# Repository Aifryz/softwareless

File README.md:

# Softwareless

What if, all software disappeared?

## Background

A few years ago, I saw a reddit post in which the OP asked if it would be possible to program a regular PC without using another PC. You would not be able to download any existing software from a network, install software from flash drives, CDs, etc.

The question also asked what would be the minimal amount of software needed to accomplish this goal.

The consensus was, that to do that you would need at least a piece of software that could write to arbitrary memory locations. From there you could write an editor, a compiler, and other software.

That answer never really satisfied me, from point of view of an embedded developer, one knows that the software running on the PC is only a small part of the puzzle. There's probably software running on the keyboard, disk drives, and of course, there's BIOS. So a modern PC probably could not be programmed without the help of any external software.

But what about designing a computer, in such a way that this would be possible?

This of course has been done in the past, first programs running on first computers could not be compiled since there were no compilers/assemblers available, ... since those would count as the first programs. Back then, people used various ways of getting programs onto computers: manually weaving wires in core rope memory, using switches in front of computers to arbitrarily modify memory, etc. So it's known that's possible, but just how hard would it be to replicate, given the last 70-ish years of progress?

## Why

With this project I want to accomplish some personal goals:

* create a RISC-V core

* create an OS

* design language and create a compiler for it

* design and develop some hardware able to support the previous goals

## Rules

* No external software can be run on the Computer
* Every automation has to be done on the Computer only
  * e.g. you cannot just compile software on a regular PC and then just type compiled program into the Computer
  * text editors are ok, just no macros, scripting, etc.
  * EDA tools can only be used to create hardware, you cannot use them to load ROMs into memory.
* No external HDL and hardware design: all HDL has to be created from scratch, same for schematics and board designs
  * I'll allow copying reference designs, provided by device manufacturers
* Omniscience: you may use every resource available to further your knowledge

Yes, I know the rules are very NIHish, I hope that by following those rules I finally get sick of reinventing the wheel and decide to use more ready libraries in the future :)

## Goals

*   Create a RISC-V processor
  * Device agnostic HDL, it has to be able to be synthesized on most of available FPGAs
*   Design and assemble terminal capable of interfacing with the designed RISC-V processor
  * keyboard
  * text display
  * CPU interface/protocol
* Design and create a basic set of software
  * text editor
  * file system
  * shell
* assembler
* Design a language and create a compiler for it
* Add a video capability to the processor system
  * text and graphics
  * some color
* Add networking
  * build a second board with working CPU
  * connect them
  * exchange data

And for the ultimate goal: I want to be able to do the thing that the computers were solely designed for, taking pictures of cats and sending them to each other :)

This list does not contain all goals that will be achieved and will be modified in time.

## Licensing

If not specified otherwise, all software in this repository is licensed under MIT license, all hardware is licensed under CERN-OHL-P
Logo is licensed under CC BY-SA 3.0

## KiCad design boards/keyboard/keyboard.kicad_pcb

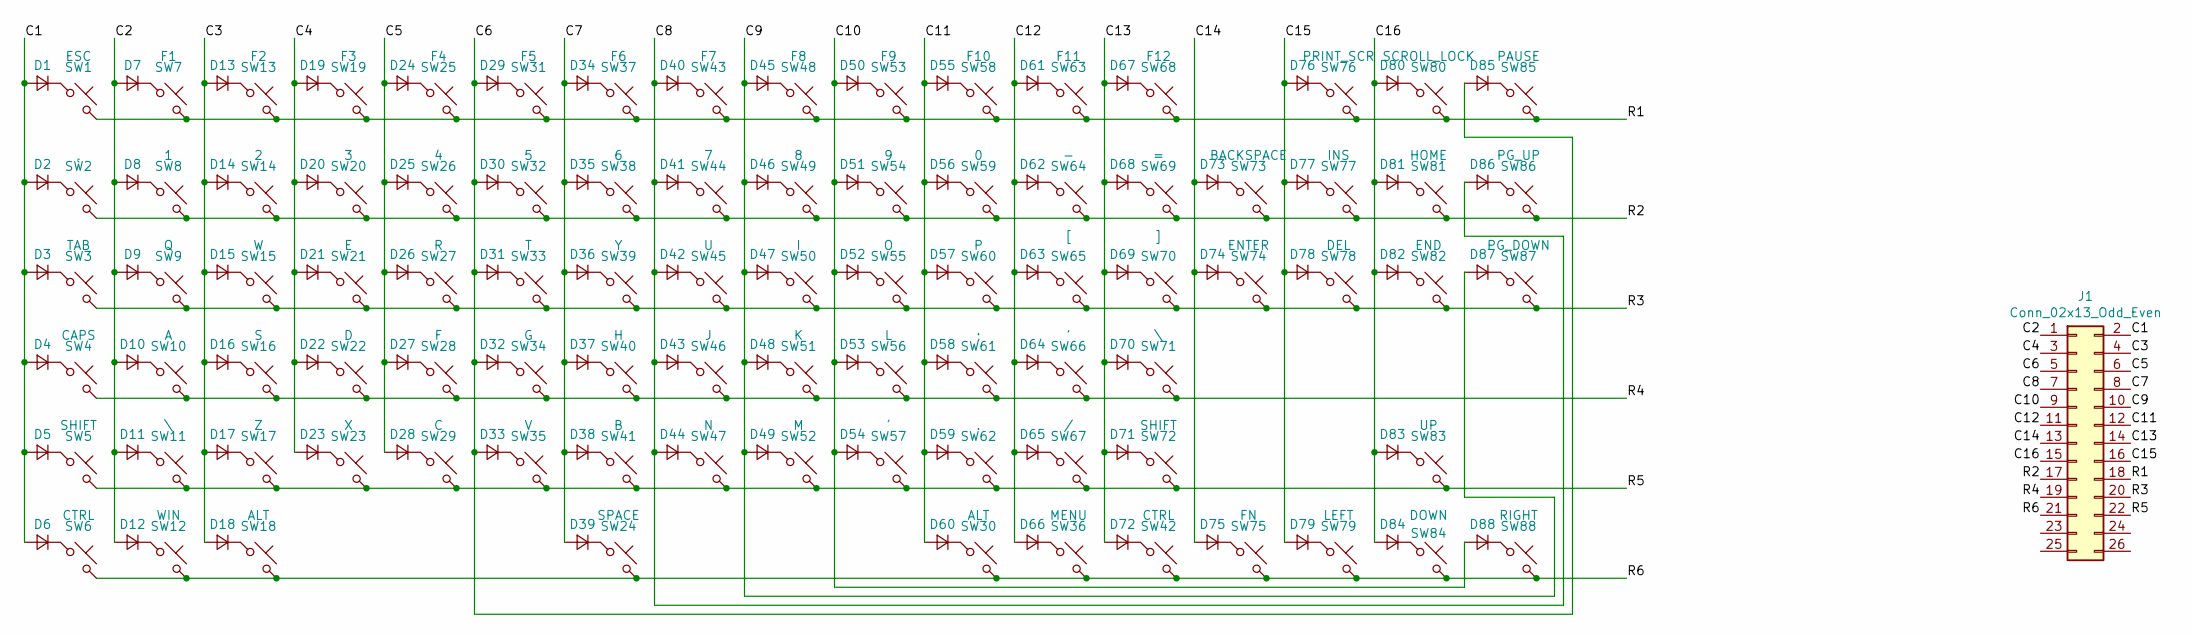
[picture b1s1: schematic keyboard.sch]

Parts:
D1, D2, D3, D4, D5, D7, D8, D9, D10, D11, D12, D13, D14, D15, D16, D17, D18, D19, D20, D21, D22, D23, D24, D25, D26, D27, D28, D29, D30, D31, D32, D33, D34, D35, D36, D37, D38, D39, D40, D41, D42, D43, D44, D45, D46, D47, D48, D49, D50, D51, D52, D53, D54, D55, D56, D57, D58, D59, D60, D61, D62, D63, D64, D65, D66, D67, D68, D69, D70, D71, D72, D73, D74, D75, D76, D77, D78, D79, D80, D81, D82, D83, D84, D85, D86, D87, D88: D_Small; D_SOD-323_HandSoldering
D6: Diode_SMD:D_SOD-323_HandSoldering; D_SOD-323_HandSoldering
J1: Conn_02x13_Odd_Even; IDC-Header_2x13_P2.54mm_Horizontal
SW1: ESC; SW_Cherry_MX_1.00u_PCB
SW2: ~`; SW_Cherry_MX_1.00u_PCB
SW3: TAB; SW_Cherry_MX_1.50u_PCB
SW4: CAPS; SW_Cherry_MX_1.75u_PCB
SW5: SHIFT; SW_Cherry_MX_1.25u_PCB
SW6: CTRL; SW_Cherry_MX_1.50u_PCB
SW7: F1; SW_Cherry_MX_1.00u_PCB
SW8: 1; SW_Cherry_MX_1.00u_PCB
SW9: Q; SW_Cherry_MX_1.00u_PCB
SW10: A; SW_Cherry_MX_1.00u_PCB
SW11, SW71: \\; SW_Cherry_MX_1.00u_PCB
SW12: WIN; SW_Cherry_MX_1.25u_PCB
SW13: F2; SW_Cherry_MX_1.00u_PCB
SW14: 2; SW_Cherry_MX_1.00u_PCB
SW15: W; SW_Cherry_MX_1.00u_PCB
SW16: S; SW_Cherry_MX_1.00u_PCB
SW17: Z; SW_Cherry_MX_1.00u_PCB
SW18: ALT; SW_Cherry_MX_1.25u_PCB
SW19: F3; SW_Cherry_MX_1.00u_PCB
SW20: 3; SW_Cherry_MX_1.00u_PCB
SW21: E; SW_Cherry_MX_1.00u_PCB
SW22: D; SW_Cherry_MX_1.00u_PCB
SW23: X; SW_Cherry_MX_1.00u_PCB
SW24: SPACE; SW_Cherry_MX_6.25u_PCB
SW25: F4; SW_Cherry_MX_1.00u_PCB
SW26: 4; SW_Cherry_MX_1.00u_PCB
SW27: R; SW_Cherry_MX_1.00u_PCB
SW28: F; SW_Cherry_MX_1.00u_PCB
SW29: C; SW_Cherry_MX_1.00u_PCB
SW30: ALT; SW_Cherry_MX_1.50u_PCB
SW31: F5; SW_Cherry_MX_1.00u_PCB
SW32: 5; SW_Cherry_MX_1.00u_PCB
SW33: T; SW_Cherry_MX_1.00u_PCB
SW34: G; SW_Cherry_MX_1.00u_PCB
SW35: V; SW_Cherry_MX_1.00u_PCB
SW36: MENU; SW_Cherry_MX_1.50u_PCB
SW37: F6; SW_Cherry_MX_1.00u_PCB
SW38: 6; SW_Cherry_MX_1.00u_PCB
SW39: Y; SW_Cherry_MX_1.00u_PCB
SW40: H; SW_Cherry_MX_1.00u_PCB
SW41: B; SW_Cherry_MX_1.00u_PCB
SW42: CTRL; SW_Cherry_MX_1.00u_PCB
SW43: F7; SW_Cherry_MX_1.00u_PCB
SW44: 7; SW_Cherry_MX_1.00u_PCB
SW45: U; SW_Cherry_MX_1.00u_PCB
SW46: J; SW_Cherry_MX_1.00u_PCB
SW47: N; SW_Cherry_MX_1.00u_PCB
SW48: F8; SW_Cherry_MX_1.00u_PCB
SW49: 8; SW_Cherry_MX_1.00u_PCB
SW50: I; SW_Cherry_MX_1.00u_PCB
SW51: K; SW_Cherry_MX_1.00u_PCB
SW52: M; SW_Cherry_MX_1.00u_PCB
SW53: F9; SW_Cherry_MX_1.00u_PCB
SW54: 9; SW_Cherry_MX_1.00u_PCB
SW55: O; SW_Cherry_MX_1.00u_PCB
SW56: L; SW_Cherry_MX_1.00u_PCB
SW57: ,; SW_Cherry_MX_1.00u_PCB
SW58: F10; SW_Cherry_MX_1.00u_PCB
SW59: 0; SW_Cherry_MX_1.00u_PCB
SW60: P; SW_Cherry_MX_1.00u_PCB
SW61: ;; SW_Cherry_MX_1.00u_PCB
SW62: .; SW_Cherry_MX_1.00u_PCB
SW63: F11; SW_Cherry_MX_1.00u_PCB
SW64: -; SW_Cherry_MX_1.00u_PCB
SW65: [; SW_Cherry_MX_1.00u_PCB
SW66: '; SW_Cherry_MX_1.00u_PCB
SW67: /; SW_Cherry_MX_1.00u_PCB
SW68: F12; SW_Cherry_MX_1.00u_PCB
SW69: =; SW_Cherry_MX_1.00u_PCB
SW70: ]; SW_Cherry_MX_1.00u_PCB
SW72: SHIFT; SW_Cherry_MX_2.75u_PCB
SW73: BACKSPACE; SW_Cherry_MX_2.00u_PCB
SW74: ENTER; SW_Cherry_MX_ISOEnter_PCB
SW75: FN; SW_Cherry_MX_1.00u_PCB
SW76: PRINT_SCR; SW_Cherry_MX_1.00u_PCB
SW77: INS; SW_Cherry_MX_1.00u_PCB
SW78: DEL; SW_Cherry_MX_1.00u_PCB
SW79: LEFT; SW_Cherry_MX_1.00u_PCB
SW80: SCROLL_LOCK; SW_Cherry_MX_1.00u_PCB
SW81: HOME; SW_Cherry_MX_1.00u_PCB
SW82: END; SW_Cherry_MX_1.00u_PCB
SW83: UP; SW_Cherry_MX_1.00u_PCB
SW84: DOWN; SW_Cherry_MX_1.00u_PCB
SW85: PAUSE; SW_Cherry_MX_1.00u_PCB
SW86: PG_UP; SW_Cherry_MX_1.00u_PCB
SW87: PG_DOWN; SW_Cherry_MX_1.00u_PCB
SW88: RIGHT; SW_Cherry_MX_1.00u_PCB

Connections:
/C1: D1.2 (A), D2.2 (A), D3.2 (A), D4.2 (A), D5.2 (A), D6.2 (A), J1.2
/C2: D7.2 (A), D8.2 (A), D9.2 (A), D10.2 (A), D11.2 (A), D12.2 (A), J1.1
/C3: D13.2 (A), D14.2 (A), D15.2 (A), D16.2 (A), D17.2 (A), D18.2 (A), J1.4
/C4: D19.2 (A), D20.2 (A), D21.2 (A), D22.2 (A), D23.2 (A), J1.3
/C5: D24.2 (A), D25.2 (A), D26.2 (A), D27.2 (A), D28.2 (A), J1.6
/C6: D29.2 (A), D30.2 (A), D31.2 (A), D32.2 (A), D33.2 (A), D85.2 (A), J1.5
/C7: D34.2 (A), D35.2 (A), D36.2 (A), D37.2 (A), D38.2 (A), D39.2 (A), J1.8
/C8: D40.2 (A), D41.2 (A), D42.2 (A), D43.2 (A), D44.2 (A), D86.2 (A), J1.7
/C9: D45.2 (A), D46.2 (A), D47.2 (A), D48.2 (A), D49.2 (A), D87.2 (A), J1.10
/C10: D50.2 (A), D51.2 (A), D52.2 (A), D53.2 (A), D54.2 (A), D88.2 (A), J1.9
/C11: D55.2 (A), D56.2 (A), D57.2 (A), D58.2 (A), D59.2 (A), D60.2 (A), J1.12
/C12: D61.2 (A), D62.2 (A), D63.2 (A), D64.2 (A), D65.2 (A), D66.2 (A), J1.11
/C13: D67.2 (A), D68.2 (A), D69.2 (A), D70.2 (A), D71.2 (A), D72.2 (A), J1.14
/C14: D73.2 (A), D74.2 (A), D75.2 (A), J1.13
/C15: D76.2 (A), D77.2 (A), D78.2 (A), D79.2 (A), J1.16
/C16: D80.2 (A), D81.2 (A), D82.2 (A), D83.2 (A), D84.2 (A), J1.15
/LED1: J1.23; also elsewhere on the board
/LED2: J1.24; also elsewhere on the board
/LED3: J1.25; also elsewhere on the board
/R1: J1.18, SW1.2, SW7.2, SW13.2, SW19.2, SW25.2, SW31.2, SW37.2, SW43.2, SW48.2, SW53.2, SW58.2, SW63.2, SW68.2, SW76.2, SW80.2, SW85.2
/R2: J1.17, SW2.2, SW8.2, SW14.2, SW20.2, SW26.2, SW32.2, SW38.2, SW44.2, SW49.2, SW54.2, SW59.2, SW64.2, SW69.2, SW73.2, SW77.2, SW81.2, SW86.2
/R3: J1.20, SW3.2, SW9.2, SW15.2, SW21.2, SW27.2, SW33.2, SW39.2, SW45.2, SW50.2, SW55.2, SW60.2, SW65.2, SW70.2, SW74.2, SW78.2, SW82.2, SW87.2
/R4: J1.19, SW4.2, SW10.2, SW16.2, SW22.2, SW28.2, SW34.2, SW40.2, SW46.2, SW51.2, SW56.2, SW61.2, SW66.2, SW71.2
/R5: J1.22, SW5.2, SW11.2, SW17.2, SW23.2, SW29.2, SW35.2, SW41.2, SW47.2, SW52.2, SW57.2, SW62.2, SW67.2, SW72.2, SW83.2
/R6: J1.21, SW6.2, SW12.2, SW18.2, SW24.2, SW30.2, SW36.2, SW42.2, SW75.2, SW79.2, SW84.2, SW88.2
GND: J1.26; also elsewhere on the board
unnamed: D1.1 (K), SW1.1
unnamed: D2.1 (K), SW2.1
unnamed: D3.1 (K), SW3.1
unnamed: D4.1 (K), SW4.1
unnamed: D5.1 (K), SW5.1
unnamed: D6.1 (K), SW6.1
unnamed: D7.1 (K), SW7.1
unnamed: D8.1 (K), SW8.1
unnamed: D9.1 (K), SW9.1
unnamed: D10.1 (K), SW10.1
unnamed: D11.1 (K), SW11.1
unnamed: D12.1 (K), SW12.1
unnamed: D13.1 (K), SW13.1
unnamed: D14.1 (K), SW14.1
unnamed: D15.1 (K), SW15.1
unnamed: D16.1 (K), SW16.1
unnamed: D17.1 (K), SW17.1
unnamed: D18.1 (K), SW18.1
unnamed: D19.1 (K), SW19.1
unnamed: D20.1 (K), SW20.1
unnamed: D21.1 (K), SW21.1
unnamed: D22.1 (K), SW22.1
unnamed: D23.1 (K), SW23.1
unnamed: D24.1 (K), SW25.1
unnamed: D25.1 (K), SW26.1
unnamed: D26.1 (K), SW27.1
unnamed: D27.1 (K), SW28.1
unnamed: D28.1 (K), SW29.1
unnamed: D29.1 (K), SW31.1
unnamed: D30.1 (K), SW32.1
unnamed: D31.1 (K), SW33.1
unnamed: D32.1 (K), SW34.1
unnamed: D33.1 (K), SW35.1
unnamed: D34.1 (K), SW37.1
unnamed: D35.1 (K), SW38.1
unnamed: D36.1 (K), SW39.1
unnamed: D37.1 (K), SW40.1
unnamed: D38.1 (K), SW41.1
unnamed: D39.1 (K), SW24.1
unnamed: D40.1 (K), SW43.1
unnamed: D41.1 (K), SW44.1
unnamed: D42.1 (K), SW45.1
unnamed: D43.1 (K), SW46.1
unnamed: D44.1 (K), SW47.1
unnamed: D45.1 (K), SW48.1
unnamed: D46.1 (K), SW49.1
unnamed: D47.1 (K), SW50.1
unnamed: D48.1 (K), SW51.1
unnamed: D49.1 (K), SW52.1
unnamed: D50.1 (K), SW53.1
unnamed: D51.1 (K), SW54.1
unnamed: D52.1 (K), SW55.1
unnamed: D53.1 (K), SW56.1
unnamed: D54.1 (K), SW57.1
unnamed: D55.1 (K), SW58.1
unnamed: D56.1 (K), SW59.1
unnamed: D57.1 (K), SW60.1
unnamed: D58.1 (K), SW61.1
unnamed: D59.1 (K), SW62.1
unnamed: D60.1 (K), SW30.1
unnamed: D61.1 (K), SW63.1
unnamed: D62.1 (K), SW64.1
unnamed: D63.1 (K), SW65.1
unnamed: D64.1 (K), SW66.1
unnamed: D65.1 (K), SW67.1
unnamed: D66.1 (K), SW36.1
unnamed: D67.1 (K), SW68.1
unnamed: D68.1 (K), SW69.1
unnamed: D69.1 (K), SW70.1
unnamed: D70.1 (K), SW71.1
unnamed: D71.1 (K), SW72.1
unnamed: D72.1 (K), SW42.1
unnamed: D73.1 (K), SW73.1
unnamed: D74.1 (K), SW74.1
unnamed: D75.1 (K), SW75.1
unnamed: D76.1 (K), SW76.1
unnamed: D77.1 (K), SW77.1
unnamed: D78.1 (K), SW78.1
unnamed: D79.1 (K), SW79.1
unnamed: D80.1 (K), SW80.1
unnamed: D81.1 (K), SW81.1
unnamed: D82.1 (K), SW82.1
unnamed: D83.1 (K), SW83.1
unnamed: D84.1 (K), SW84.1
unnamed: D85.1 (K), SW85.1
unnamed: D86.1 (K), SW86.1
unnamed: D87.1 (K), SW87.1
unnamed: D88.1 (K), SW88.1

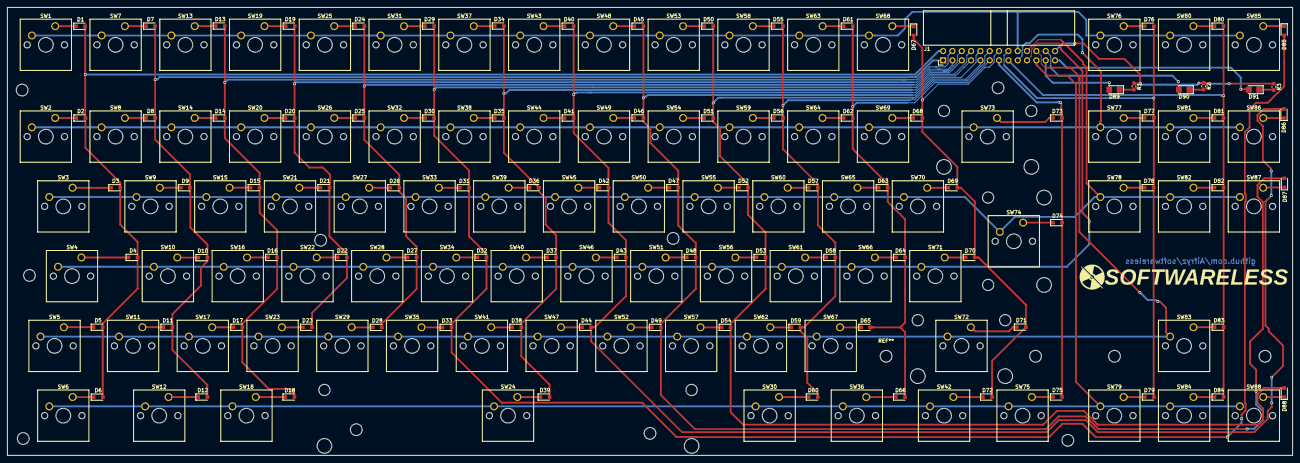
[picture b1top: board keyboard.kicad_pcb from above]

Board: 2 copper layers, 350.0 x 122.0 mm, 183 parts (0 on the bottom side), 117 nets.

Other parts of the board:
D89, D90, D91: LED; LED_1206_3216Metric_Castellated
R1, R2, R3: 330R; R_0603_1608Metric_Pad1.05x0.95mm_HandSolder

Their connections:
/LED1: D89.2; also elsewhere on the board
/LED2: D90.2; also elsewhere on the board
/LED3: D91.2; also elsewhere on the board
GND: R1.1, R2.1, R3.1; also elsewhere on the board
unnamed: D89.1, R1.2
unnamed: D90.1, R2.2
unnamed: D91.1, R3.2

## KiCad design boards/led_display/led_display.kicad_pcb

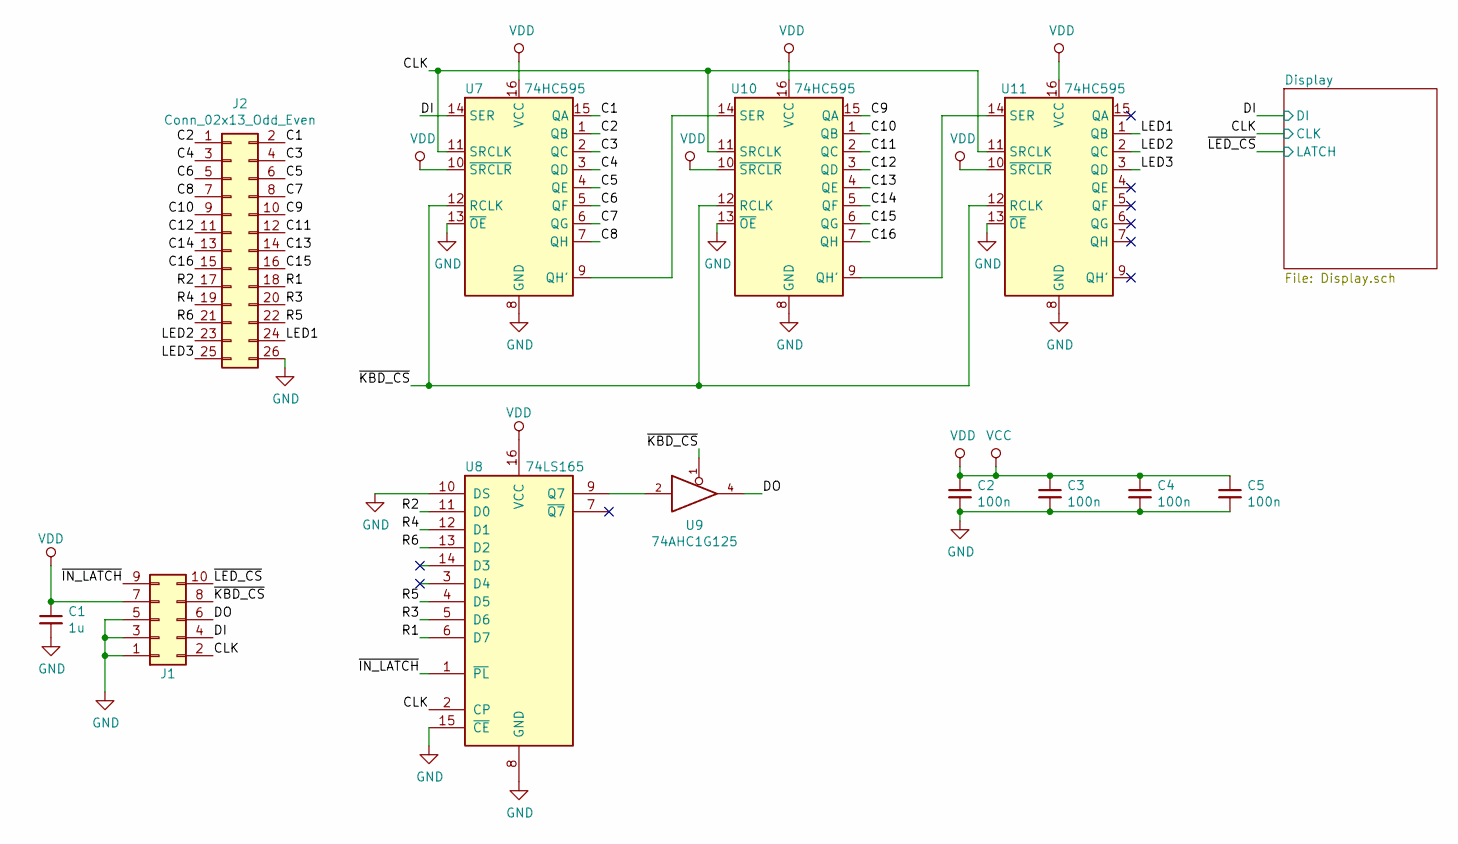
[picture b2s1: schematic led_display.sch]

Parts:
C1: 1u; C_0805_2012Metric
C2, C3, C4, C5: 100n; C_0603_1608Metric
J1: Conn_02x05_Odd_Even; IDC-Header_2x05_P2.54mm_Vertical
J2: Conn_02x13_Odd_Even; IDC-Header_2x13_P2.54mm_Vertical
U7, U10, U11: 74HC595; SOIC-16_3.9x9.9mm_P1.27mm
U8: 74LS165; SOIC-16_3.9x9.9mm_P1.27mm
U9: 74AHC1G125; SOT-23-5

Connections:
/C1: J2.2, U7.15 (QA)
/C2: J2.1, U7.1 (QB)
/C3: J2.4, U7.2 (QC)
/C4: J2.3, U7.3 (QD)
/C5: J2.6, U7.4 (QE)
/C6: J2.5, U7.5 (QF)
/C7: J2.8, U7.6 (QG)
/C8: J2.7, U7.7 (QH)
/C9: J2.10, U10.15 (QA)
/C10: J2.9, U10.1 (QB)
/C11: J2.12, U10.2 (QC)
/C12: J2.11, U10.3 (QD)
/C13: J2.14, U10.4 (QE)
/C14: J2.13, U10.5 (QF)
/C15: J2.16, U10.6 (QG)
/C16: J2.15, U10.7 (QH)
/CLK: J1.2, U7.11 (SRCLK), U8.2 (CP), U10.11 (SRCLK), U11.11 (SRCLK); also elsewhere on the board
/DI: J1.4, U7.14 (SER); also elsewhere on the board
/DO: J1.6, U9.4
/LED1: J2.24, U11.1 (QB)
/LED2: J2.23, U11.2 (QC)
/LED3: J2.25, U11.3 (QD)
/R1: J2.18, U8.6 (D7)
/R2: J2.17, U8.11 (D0)
/R3: J2.20, U8.5 (D6)
/R4: J2.19, U8.12 (D1)
/R5: J2.22, U8.4 (D5)
/R6: J2.21, U8.13 (D2)
/~IN_LATCH: J1.9, U8.1 (~PL)
/~KBD_CS: J1.8, U7.12 (RCLK), U9.1, U10.12 (RCLK), U11.12 (RCLK)
/~LED_CS: J1.10; also elsewhere on the board
GND: C1.2, C2.2, C3.2, C4.2, C5.2, J1.1, J1.3, J1.5, J2.26, U7.8 (GND), U7.13 (~OE), U8.8 (GND), U8.10 (DS), U8.15 (~CE), U9.3 (GND), U10.8 (GND), U10.13 (~OE), U11.8 (GND), U11.13 (~OE); also elsewhere on the board
unnamed: U8.9 (Q7), U9.2
unnamed: U10.9 (QH'), U11.14 (SER)
unnamed: U7.9 (QH'), U10.14 (SER)
VCC: C1.1, C2.1, C3.1, C4.1, C5.1, J1.7, U7.10 (~SRCLR), U7.16 (VCC), U8.16 (VCC), U9.5 (VCC), U10.10 (~SRCLR), U10.16 (VCC), U11.10 (~SRCLR), U11.16 (VCC); also elsewhere on the board

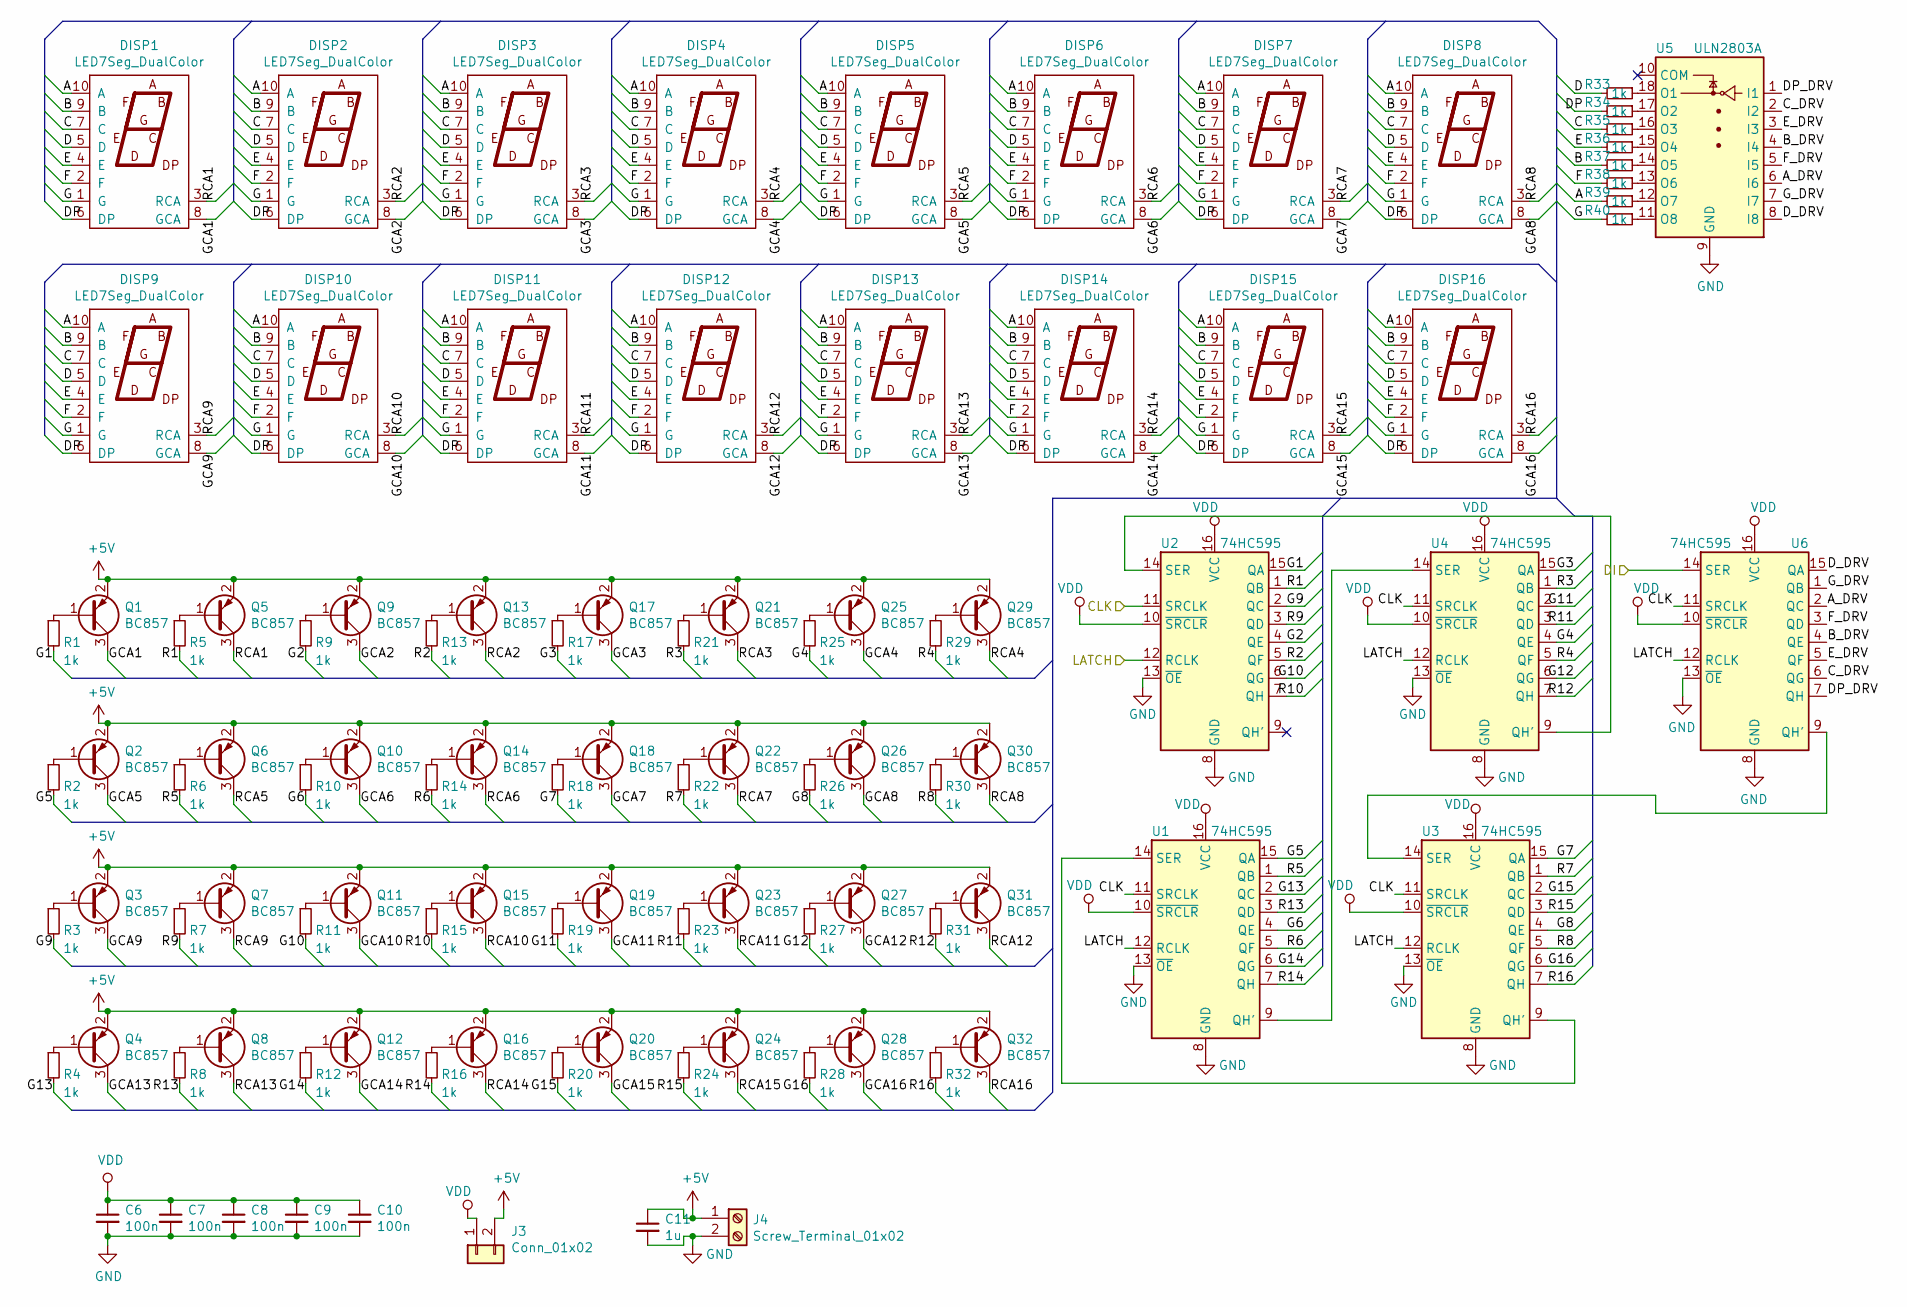
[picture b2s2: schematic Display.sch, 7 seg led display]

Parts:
C6, C7, C8, C9, C10: 100n; C_0603_1608Metric
C11: 1u; C_0805_2012Metric
DISP1, DISP2, DISP3, DISP4, DISP5, DISP6, DISP7, DISP8, DISP9, DISP10, DISP11, DISP12, DISP13, DISP14, DISP15, DISP16: LED7Seg_DualColor; LED7Seg_Vertical_039inch
J3: Conn_01x02; PinHeader_1x02_P2.54mm_Vertical
J4: Screw_Terminal_01x02; TerminalBlock_bornier-2_P5.08mm
Q1, Q2, Q3, Q4, Q5, Q6, Q7, Q8, Q9, Q10, Q11, Q12, Q13, Q14, Q15, Q16, Q17, Q18, Q19, Q20, Q21, Q22, Q23, Q24, Q25, Q26, Q27, Q28, Q29, Q30, Q31, Q32: BC857; SOT-23
R1, R2, R3, R4, R5, R6, R7, R8, R9, R10, R11, R12, R13, R14, R15, R16, R17, R18, R19, R20, R21, R22, R23, R24, R25, R26, R27, R28, R29, R30, R31, R32, R33, R34, R35, R36, R37, R38, R39, R40: 1k; R_0603_1608Metric
U1, U2, U3, U4, U6: 74HC595; SOIC-16_3.9x9.9mm_P1.27mm
U5: ULN2803A; SOIC-18W_7.5x11.6mm_P1.27mm

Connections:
+5V: C11.1, J3.2, J4.1, Q1.2 (E), Q2.2 (E), Q3.2 (E), Q4.2 (E), Q5.2 (E), Q6.2 (E), Q7.2 (E), Q8.2 (E), Q9.2 (E), Q10.2 (E), Q11.2 (E), Q12.2 (E), Q13.2 (E), Q14.2 (E), Q15.2 (E), Q16.2 (E), Q17.2 (E), Q18.2 (E), Q19.2 (E), Q20.2 (E), Q21.2 (E), Q22.2 (E), Q23.2 (E), Q24.2 (E), Q25.2 (E), Q26.2 (E), Q27.2 (E), Q28.2 (E), Q29.2 (E), Q30.2 (E), Q31.2 (E), Q32.2 (E)
/CLK: U1.11 (SRCLK), U2.11 (SRCLK), U3.11 (SRCLK), U4.11 (SRCLK), U6.11 (SRCLK); also elsewhere on the board
/DI: U6.14 (SER); also elsewhere on the board
/Display/A: DISP1.10 (A), DISP2.10 (A), DISP3.10 (A), DISP4.10 (A), DISP5.10 (A), DISP6.10 (A), DISP7.10 (A), DISP8.10 (A), DISP9.10 (A), DISP10.10 (A), DISP11.10 (A), DISP12.10 (A), DISP13.10 (A), DISP14.10 (A), DISP15.10 (A), DISP16.10 (A), R39.2
/Display/A_DRV: U5.6 (I6), U6.2 (QC)
/Display/B: DISP1.9 (B), DISP2.9 (B), DISP3.9 (B), DISP4.9 (B), DISP5.9 (B), DISP6.9 (B), DISP7.9 (B), DISP8.9 (B), DISP9.9 (B), DISP10.9 (B), DISP11.9 (B), DISP12.9 (B), DISP13.9 (B), DISP14.9 (B), DISP15.9 (B), DISP16.9 (B), R37.2
/Display/B_DRV: U5.4 (I4), U6.4 (QE)
/Display/C: DISP1.7 (C), DISP2.7 (C), DISP3.7 (C), DISP4.7 (C), DISP5.7 (C), DISP6.7 (C), DISP7.7 (C), DISP8.7 (C), DISP9.7 (C), DISP10.7 (C), DISP11.7 (C), DISP12.7 (C), DISP13.7 (C), DISP14.7 (C), DISP15.7 (C), DISP16.7 (C), R35.2
/Display/C_DRV: U5.2 (I2), U6.6 (QG)
/Display/D: DISP1.5 (D), DISP2.5 (D), DISP3.5 (D), DISP4.5 (D), DISP5.5 (D), DISP6.5 (D), DISP7.5 (D), DISP8.5 (D), DISP9.5 (D), DISP10.5 (D), DISP11.5 (D), DISP12.5 (D), DISP13.5 (D), DISP14.5 (D), DISP15.5 (D), DISP16.5 (D), R33.2
/Display/DP: DISP1.6 (DP), DISP2.6 (DP), DISP3.6 (DP), DISP4.6 (DP), DISP5.6 (DP), DISP6.6 (DP), DISP7.6 (DP), DISP8.6 (DP), DISP9.6 (DP), DISP10.6 (DP), DISP11.6 (DP), DISP12.6 (DP), DISP13.6 (DP), DISP14.6 (DP), DISP15.6 (DP), DISP16.6 (DP), R34.2
/Display/DP_DRV: U5.1 (I1), U6.7 (QH)
/Display/D_DRV: U5.8 (I8), U6.15 (QA)
/Display/E: DISP1.4 (E), DISP2.4 (E), DISP3.4 (E), DISP4.4 (E), DISP5.4 (E), DISP6.4 (E), DISP7.4 (E), DISP8.4 (E), DISP9.4 (E), DISP10.4 (E), DISP11.4 (E), DISP12.4 (E), DISP13.4 (E), DISP14.4 (E), DISP15.4 (E), DISP16.4 (E), R36.2
/Display/E_DRV: U5.3 (I3), U6.5 (QF)
/Display/F: DISP1.2 (F), DISP2.2 (F), DISP3.2 (F), DISP4.2 (F), DISP5.2 (F), DISP6.2 (F), DISP7.2 (F), DISP8.2 (F), DISP9.2 (F), DISP10.2 (F), DISP11.2 (F), DISP12.2 (F), DISP13.2 (F), DISP14.2 (F), DISP15.2 (F), DISP16.2 (F), R38.2
/Display/F_DRV: U5.5 (I5), U6.3 (QD)
/Display/G: DISP1.1 (G), DISP2.1 (G), DISP3.1 (G), DISP4.1 (G), DISP5.1 (G), DISP6.1 (G), DISP7.1 (G), DISP8.1 (G), DISP9.1 (G), DISP10.1 (G), DISP11.1 (G), DISP12.1 (G), DISP13.1 (G), DISP14.1 (G), DISP15.1 (G), DISP16.1 (G), R40.2
/Display/G1: R1.2, U2.15 (QA)
/Display/G2: R9.2, U2.4 (QE)
/Display/G3: R17.2, U4.15 (QA)
/Display/G4: R25.2, U4.4 (QE)
/Display/G5: R2.2, U1.15 (QA)
/Display/G6: R10.2, U1.4 (QE)
/Display/G7: R18.2, U3.15 (QA)
/Display/G8: R26.2, U3.4 (QE)
/Display/G9: R3.2, U2.2 (QC)
/Display/G10: R11.2, U2.6 (QG)
/Display/G11: R19.2, U4.2 (QC)
/Display/G12: R27.2, U4.6 (QG)
/Display/G13: R4.2, U1.2 (QC)
/Display/G14: R12.2, U1.6 (QG)
/Display/G15: R20.2, U3.2 (QC)
/Display/G16: R28.2, U3.6 (QG)
/Display/GCA1: DISP1.8 (GCA), Q1.3 (C)
/Display/GCA2: DISP2.8 (GCA), Q9.3 (C)
/Display/GCA3: DISP3.8 (GCA), Q17.3 (C)
/Display/GCA4: DISP4.8 (GCA), Q25.3 (C)
/Display/GCA5: DISP5.8 (GCA), Q2.3 (C)
/Display/GCA6: DISP6.8 (GCA), Q10.3 (C)
/Display/GCA7: DISP7.8 (GCA), Q18.3 (C)
/Display/GCA8: DISP8.8 (GCA), Q26.3 (C)
/Display/GCA9: DISP9.8 (GCA), Q3.3 (C)
/Display/GCA10: DISP10.8 (GCA), Q11.3 (C)
/Display/GCA11: DISP11.8 (GCA), Q19.3 (C)
/Display/GCA12: DISP12.8 (GCA), Q27.3 (C)
/Display/GCA13: DISP13.8 (GCA), Q4.3 (C)
/Display/GCA14: DISP14.8 (GCA), Q12.3 (C)
/Display/GCA15: DISP15.8 (GCA), Q20.3 (C)
/Display/GCA16: DISP16.8 (GCA), Q28.3 (C)
/Display/G_DRV: U5.7 (I7), U6.1 (QB)
/Display/R1: R5.2, U2.1 (QB)
/Display/R2: R13.2, U2.5 (QF)
/Display/R3: R21.2, U4.1 (QB)
/Display/R4: R29.2, U4.5 (QF)
/Display/R5: R6.2, U1.1 (QB)
/Display/R6: R14.2, U1.5 (QF)
/Display/R7: R22.2, U3.1 (QB)
/Display/R8: R30.2, U3.5 (QF)
/Display/R9: R7.2, U2.3 (QD)
/Display/R10: R15.2, U2.7 (QH)
/Display/R11: R23.2, U4.3 (QD)
/Display/R12: R31.2, U4.7 (QH)
/Display/R13: R8.2, U1.3 (QD)
/Display/R14: R16.2, U1.7 (QH)
/Display/R15: R24.2, U3.3 (QD)
/Display/R16: R32.2, U3.7 (QH)
/Display/RCA1: DISP1.3 (RCA), Q5.3 (C)
/Display/RCA2: DISP2.3 (RCA), Q13.3 (C)
/Display/RCA3: DISP3.3 (RCA), Q21.3 (C)
/Display/RCA4: DISP4.3 (RCA), Q29.3 (C)
/Display/RCA5: DISP5.3 (RCA), Q6.3 (C)
/Display/RCA6: DISP6.3 (RCA), Q14.3 (C)
/Display/RCA7: DISP7.3 (RCA), Q22.3 (C)
/Display/RCA8: DISP8.3 (RCA), Q30.3 (C)
/Display/RCA9: DISP9.3 (RCA), Q7.3 (C)
/Display/RCA10: DISP10.3 (RCA), Q15.3 (C)
/Display/RCA11: DISP11.3 (RCA), Q23.3 (C)
/Display/RCA12: DISP12.3 (RCA), Q31.3 (C)
/Display/RCA13: DISP13.3 (RCA), Q8.3 (C)
/Display/RCA14: DISP14.3 (RCA), Q16.3 (C)
/Display/RCA15: DISP15.3 (RCA), Q24.3 (C)
/Display/RCA16: DISP16.3 (RCA), Q32.3 (C)
/~LED_CS: U1.12 (RCLK), U2.12 (RCLK), U3.12 (RCLK), U4.12 (RCLK), U6.12 (RCLK); also elsewhere on the board
GND: C6.2, C7.2, C8.2, C9.2, C10.2, C11.2, J4.2, U1.8 (GND), U1.13 (~OE), U2.8 (GND), U2.13 (~OE), U3.8 (GND), U3.13 (~OE), U4.8 (GND), U4.13 (~OE), U5.9 (GND), U6.8 (GND), U6.13 (~OE); also elsewhere on the board
unnamed: Q1.1 (B), R1.1
unnamed: Q2.1 (B), R2.1
unnamed: Q3.1 (B), R3.1
unnamed: Q4.1 (B), R4.1
unnamed: Q5.1 (B), R5.1
unnamed: Q6.1 (B), R6.1
unnamed: Q7.1 (B), R7.1
unnamed: Q8.1 (B), R8.1
unnamed: Q9.1 (B), R9.1
unnamed: Q10.1 (B), R10.1
unnamed: Q11.1 (B), R11.1
unnamed: Q12.1 (B), R12.1
unnamed: Q13.1 (B), R13.1
unnamed: Q14.1 (B), R14.1
unnamed: Q15.1 (B), R15.1
unnamed: Q16.1 (B), R16.1
unnamed: Q17.1 (B), R17.1
unnamed: Q18.1 (B), R18.1
unnamed: Q19.1 (B), R19.1
unnamed: Q20.1 (B), R20.1
unnamed: Q21.1 (B), R21.1
unnamed: Q22.1 (B), R22.1
unnamed: Q23.1 (B), R23.1
unnamed: Q24.1 (B), R24.1
unnamed: Q25.1 (B), R25.1
unnamed: Q26.1 (B), R26.1
unnamed: Q27.1 (B), R27.1
unnamed: Q28.1 (B), R28.1
unnamed: Q29.1 (B), R29.1
unnamed: Q30.1 (B), R30.1
unnamed: Q31.1 (B), R31.1
unnamed: Q32.1 (B), R32.1
unnamed: R33.1, U5.18 (O1)
unnamed: R34.1, U5.17 (O2)
unnamed: R35.1, U5.16 (O3)
unnamed: R36.1, U5.15 (O4)
unnamed: R37.1, U5.14 (O5)
unnamed: R38.1, U5.13 (O6)
unnamed: R39.1, U5.12 (O7)
unnamed: R40.1, U5.11 (O8)
unnamed: U1.9 (QH'), U4.14 (SER)
unnamed: U1.14 (SER), U3.9 (QH')
unnamed: U2.14 (SER), U4.9 (QH')
unnamed: U3.14 (SER), U6.9 (QH')
VCC: C6.1, C7.1, C8.1, C9.1, C10.1, J3.1, U1.10 (~SRCLR), U1.16 (VCC), U2.10 (~SRCLR), U2.16 (VCC), U3.10 (~SRCLR), U3.16 (VCC), U4.10 (~SRCLR), U4.16 (VCC), U6.10 (~SRCLR), U6.16 (VCC); also elsewhere on the board

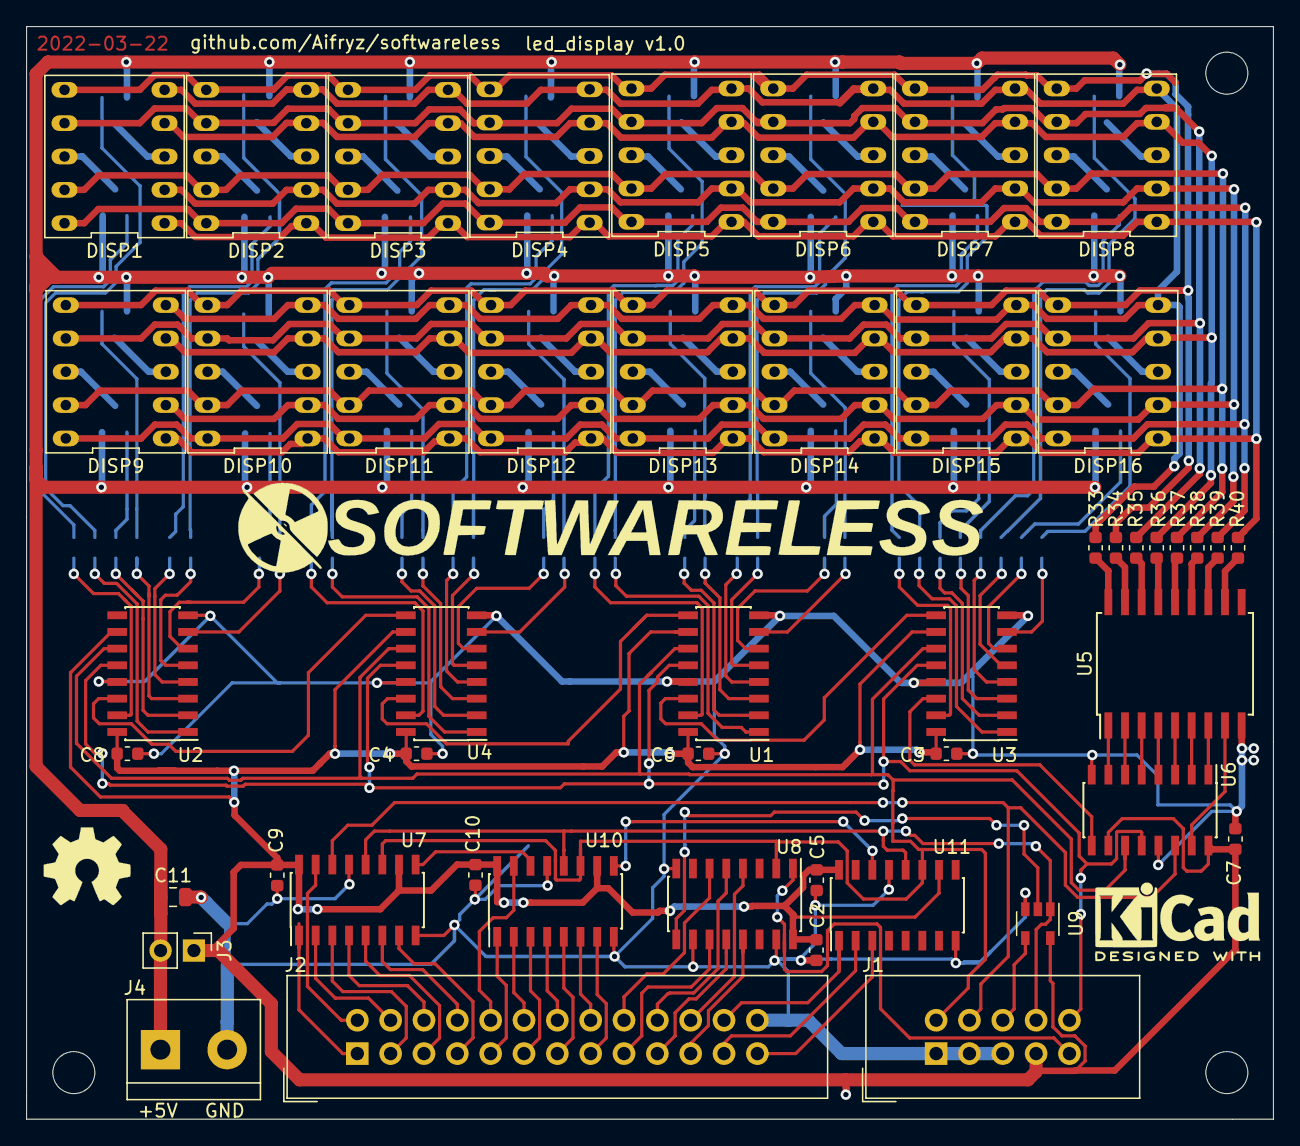
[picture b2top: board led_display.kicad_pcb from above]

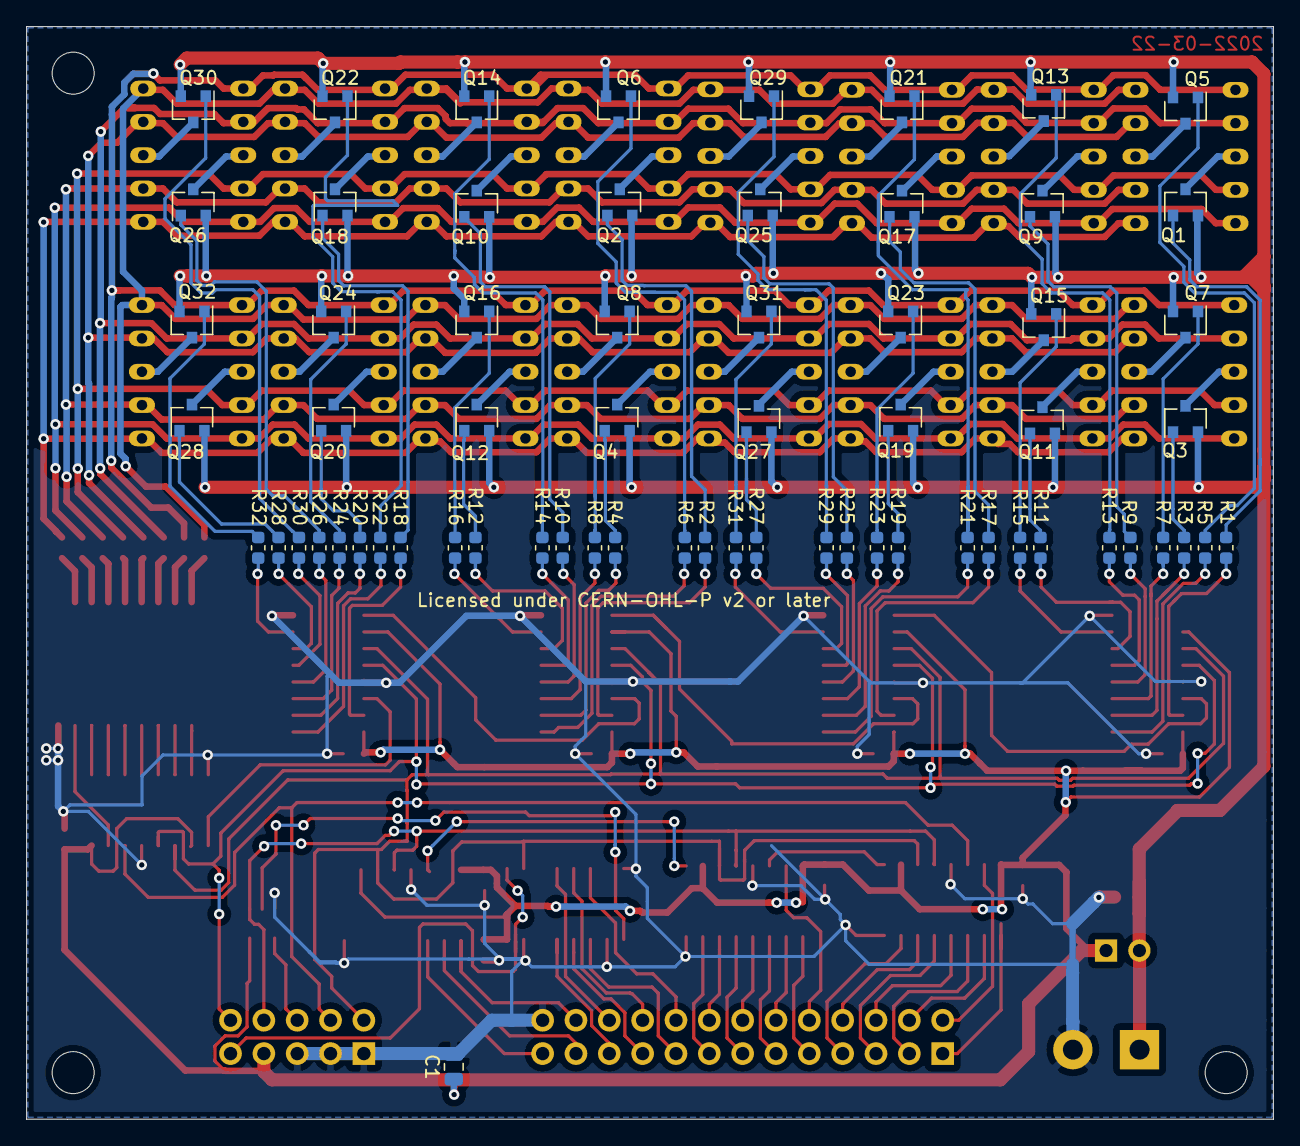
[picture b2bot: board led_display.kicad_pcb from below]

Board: 2 copper layers, 95.0 x 83.2 mm, 114 parts (65 on the bottom side), 161 nets.

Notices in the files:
boards/keyboard/keyboard.kicad_pcb:
Licensed under CERN-OHL-P v2 or later
